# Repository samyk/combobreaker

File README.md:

# [C-C-C-C-Combo Breaker](http://samy.pl/combobreaker/)

**[Combo Breaker](http://samy.pl/combobreaker/)** is a motorized, battery powered, 3D printed, Arduino-based combination lock cracking device. It is portable, open source, 3D models provided, and exploits a new technique I've discovered for [cracking combination locks in 8 attempts or less](https://www.youtube.com/watch?v=09UgmwtL12c), but in an even more exciting, automated fashion.

By [@SamyKamkar](https://twitter.com/samykamkar)

#### Follow me on [Twitter](https://twitter.com/samykamkar) or [join my mailing list](http://samy.pl/list/) to hear about future projects and research.

**Live demonstration** and full details available in [the video](https://www.youtube.com/watch?v=YcpSvHpbHQ4):

-----

**Point of Contact:** [@SamyKamkar](https://twitter.com/samykamkar) // <http://samy.pl>

**Video demonstration / explanation:** [https://youtu.be/YcpSvHpbHQ4](https://youtu.be/YcpSvHpbHQ4)

**Released:** May 14, 2015

**Source code / 3D models:** [https://github.com/samyk/combobreaker](https://github.com/samyk/combobreaker)

**Unit Cost:** < $100

**Status:** Operational, open source, open hardware, declassified.

-----

# (U) Hardware

### [Arduino Nano](http://amzn.to/1QLlf23)
**$12**: A [5V Arduino Nano](http://amzn.to/1QLlf23) microcontroller is used as the brains of the project.

### [Allegro A3967 / EasyDriver Stepper Driver](http://amzn.to/1A1Ovxl)
**$20**: I originally used an A3967-based [EasyDriver](http://amzn.to/1A1Ovxl) which can drive a stepper motor up to 30V at 750mA. This is what precisely controls the dial.

### or [Allegro A4988](http://amzn.to/1L3q7fK)
**$7**: Instead of the EasyDriver, I upgraded to a smaller, yet more powerful stepper driver that can go up to 1 amp (1000mA).

### [Stepper Motor](http://amzn.to/1FfLUQG)
**$30**: You can use a normal stepper motor for the "simpler" version of the Combo Breaker build, however if you're working on creating the more advanced version, you'll need a double-shaft stepper motor like I liste below.

### or [Double Shaft Stepper Motor](http://www.phidgets.com/products.php?product_id=3320)
**$16**: This double shaft stepper motor allows you to build the more advanced Combo Breaker while employing an optical rotary encoder on the back to detect the position of the stepper when the dial stops turning (which is part of the exploit employed).

### [HKT22 Optical Rotary Encoder](http://www.phidgets.com/products.php?product_id=3531)
**$25**: For use **only** with the double shaft stepper motor, this optical rotary encoder lets us know what position the shaft of the stepper motor is at and allows us to employ an exploit on Master combination locks where the stepper will get locked into certain grooves within the internal combination disc of the lock.

### [Analog Feedback Servo](https://www.adafruit.com/products/1404)
**$15**: This servo not only provides the torque we need to lift the shackle (90.26 oz*in), but has an additional wire providing analog feedback that we use to detect the state of the shackle and whether it has opened or not.

### [L7805 Voltage Regulators](http://amzn.to/1A28XOt)
**$6**: If you're using the analog feedback servo, you'll want to use an external voltage regulator to provide enough juice to the servo. While the Arduino is 5V and can drive the servo normally, it won't be able to pump out enough current for the servo when it starts hitting the shackle and could damage your Arduino.

### [500mAh 3S Lipo Battery](http://amzn.to/1PkRVlz)
**$20**: This 500mAh 3S (3-cell, 11.1V) battery gives enough juice to the stepper motor to be very effective, and at 500mAh can last between 30-120minutes straight before having to be recharged.

### [Lipo Charger](http://amzn.to/1A1Q2n7)
**$50**: This lipo charger is overkill if only used for this project, but is a good one that I use at home for a wide range of batteries and cells. You don't need this one, but if you want to recharge the battery, you'll need a charger that supports 3-cell LiPos.

### [Arctic Alumina Thermal Adehsive](http://amzn.to/1PkTakG)
**$8**: Not required, but this is the thermal **adhesive** I use to **permanently** attach the heatsink to the stepper motor driver. Normal thermal paste has very little adhesion and kept falling off, so I switched from thermal paste to this thermal adhesive.

### [Digital Calipers](http://amzn.to/1K8juex)
**$16**: If you don't already have digital calipers for precise measurements to measure the lock, for example, these are inexpensive and accurate.

### [Breadboard and Wires](http://amzn.to/1FfMb6e)
**$6**: If you don't already have a breadboard and wires, they will kind of help.

-----

# (U) Software

### Combo Breaker
Combo Breaker's source code can be obtained in entirety from my github: <https://github.com/samyk/combobreaker>

-----

# (U) 3D Models

I've included the 3D models on my github: <https://github.com/samyk/combobreaker>

-----

# (U) Contact

**Point of Contact:** [@SamyKamkar](https://twitter.com/samykamkar)

You can see more of my projects at <http://samy.pl>.

#### Follow me on [Twitter](https://twitter.com/samykamkar) or [join my mailing list](http://samy.pl/list/) to hear about future projects and research.

Thanks!

------

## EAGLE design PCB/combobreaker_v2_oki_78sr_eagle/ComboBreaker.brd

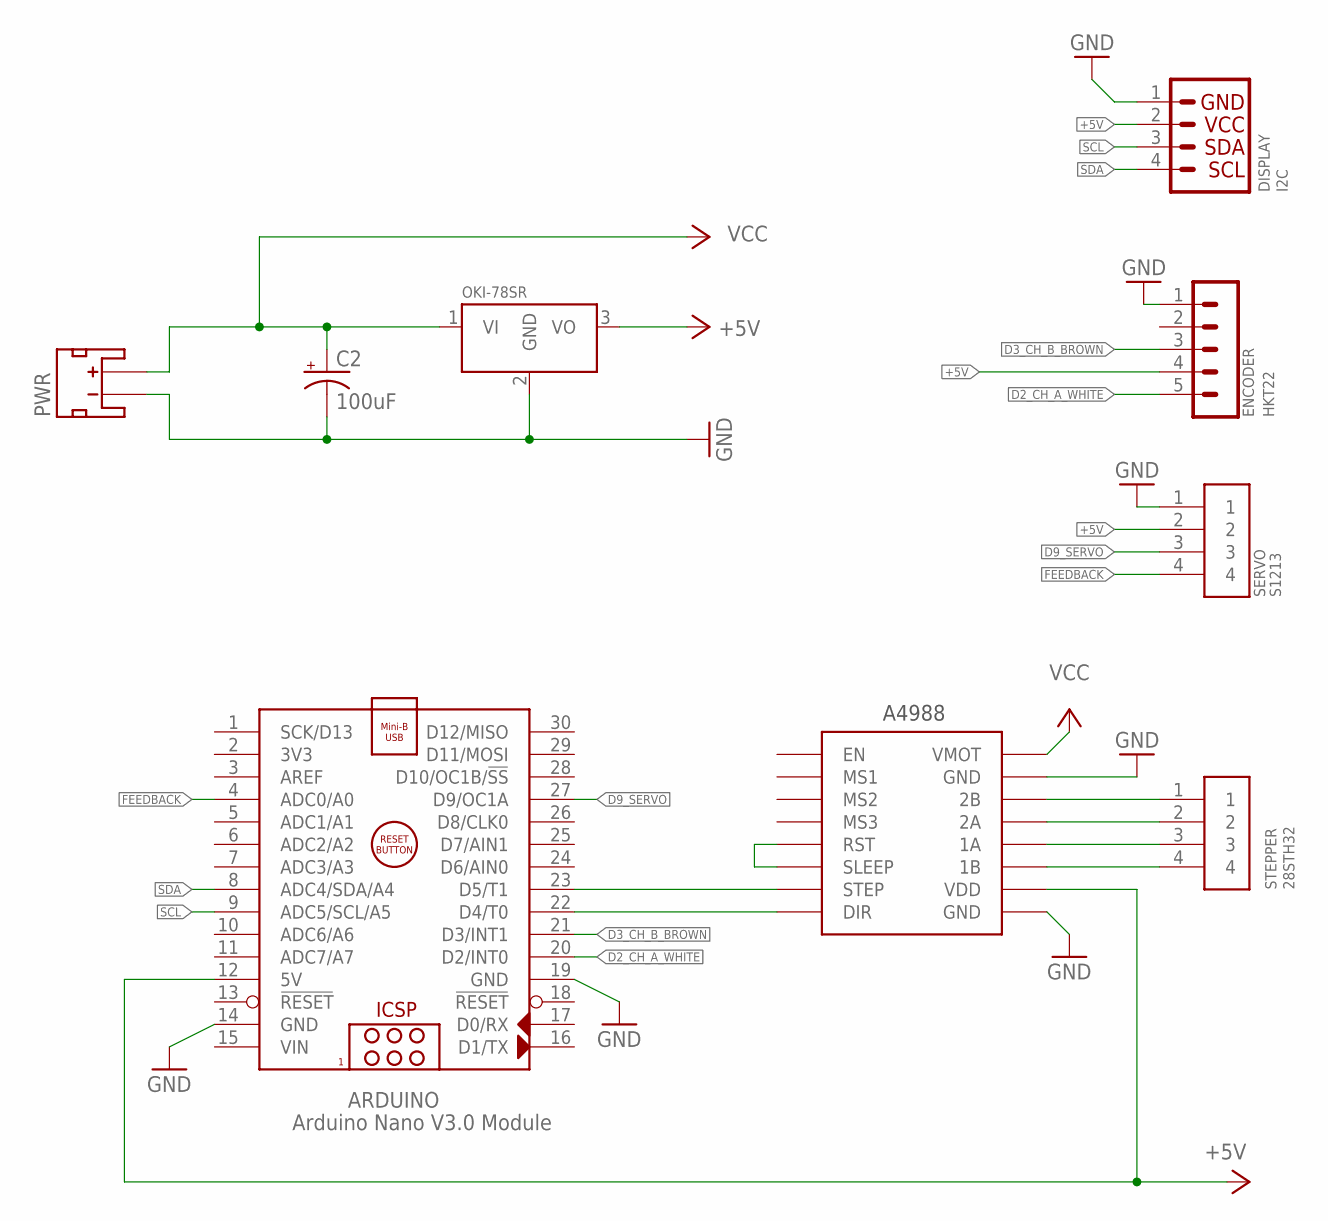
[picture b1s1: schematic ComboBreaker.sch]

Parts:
A4988: StepStick; A4988BREAKOUT
ARDUINO: Arduino Nano V3.0 Module; ARDUINO_NANO
C2: 100uF; E3,5-8
DISPLAY: I2C; 1X04
ENCODER: HKT22; CON-LSTB_MA05-1
OKI-78SR: 5/1.5-W36H-C; OKI-78SRH
PWR: 7-35v; JST-2-SMD
SERVO: S1213; ADAFRUIT_1X04-BIG
STEPPER: 28STH32; ADAFRUIT_1X04-BIG

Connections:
1A_GRN: A4988.1A, STEPPER.3
1B_BLK: A4988.1B, STEPPER.4
2A_RED: A4988.2A, STEPPER.2
2B_BLU: A4988.2B, STEPPER.1
+5V: A4988.VDD, ARDUINO.12 (5V), DISPLAY.2, ENCODER.4, OKI-78SR.3 (VO), SERVO.2
D2_CH_A_WHITE: ARDUINO.20 (D2/INT0), ENCODER.5
D3_CH_B_BROWN: ARDUINO.21 (D3/INT1), ENCODER.3
D9_SERVO: ARDUINO.27 (D9/OC1A), SERVO.3
FEEDBACK: ARDUINO.4 (ADC0/A0), SERVO.4
GND: A4988.GND, A4988.GND@0 (GND), ARDUINO.14 (GND), ARDUINO.19 (GND), C2.-, DISPLAY.1, ENCODER.1, OKI-78SR.2 (GND), PWR.GND (-), SERVO.1
unnamed: A4988.RST, A4988.SLP (SLEEP)
unnamed: A4988.DIR, ARDUINO.22 (D4/T0)
unnamed: A4988.STEP, ARDUINO.23 (D5/T1)
SCL: ARDUINO.9 (ADC5/SCL/A5), DISPLAY.3
SDA: ARDUINO.8 (ADC4/SDA/A4), DISPLAY.4
VCC: A4988.VMOT, C2.+, OKI-78SR.1 (VI), PWR.2 (+)
VIN: ARDUINO.15 (VIN)

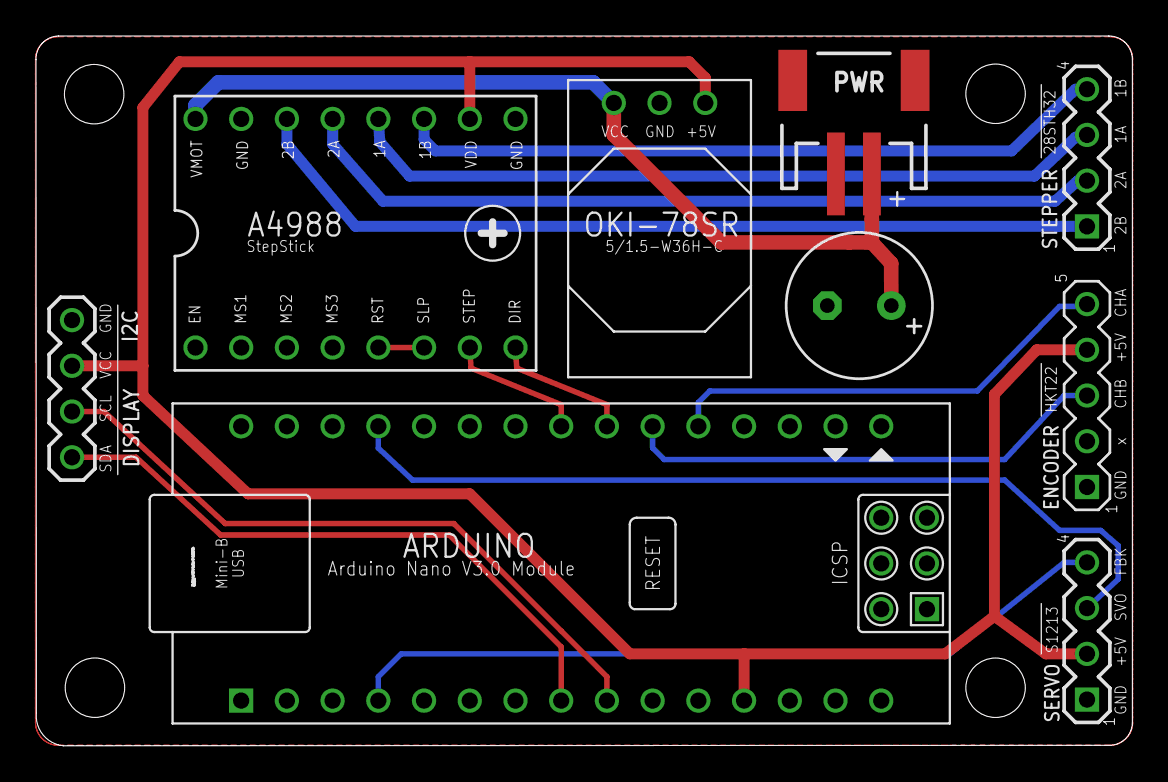
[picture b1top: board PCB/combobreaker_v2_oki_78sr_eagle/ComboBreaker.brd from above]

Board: 2 copper layers, 60.9 x 39.4 mm, 15 parts (1 on the bottom side), 16 nets.

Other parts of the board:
U$1, U$2, U$3, U$4: STAND-OFF
U$5: AM
U$6: MASTERLOCK2

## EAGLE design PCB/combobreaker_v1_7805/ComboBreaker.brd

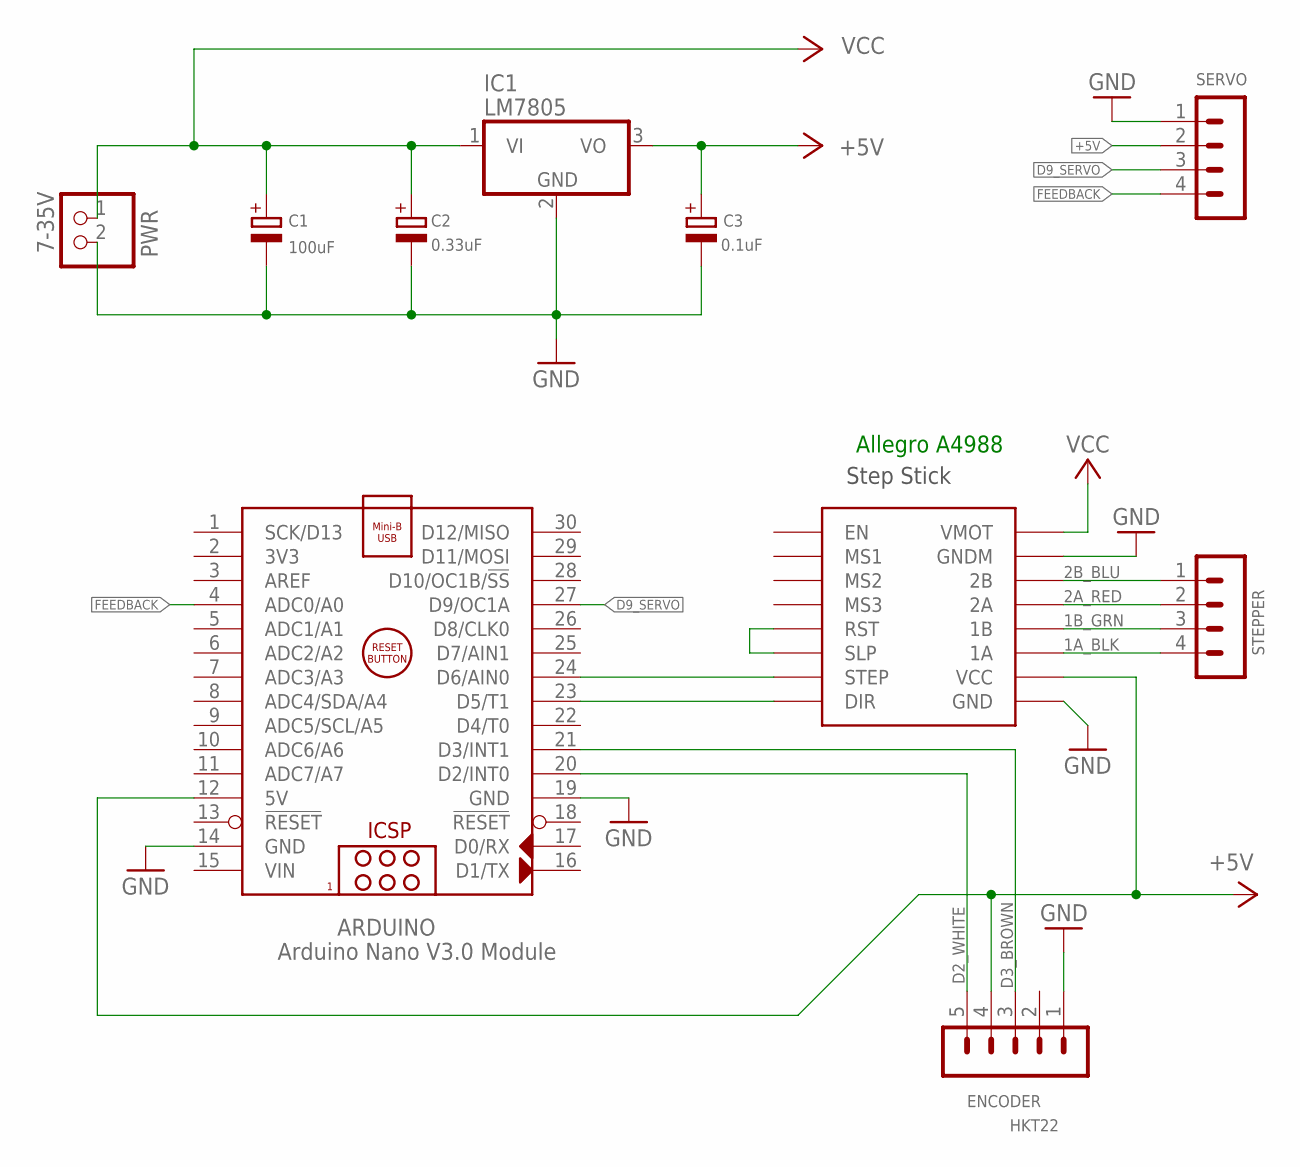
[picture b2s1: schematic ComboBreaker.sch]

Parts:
ARDUINO: Arduino Nano V3.0 Module; ARDUINO_NANO
C1: 100uF; E2-4
C2: 0.33uF; E2-4
C3: 0.1uF; E2-4
ENCODER: HKT22; MA05-1
IC1: LM7805; TO220V
PWR: 7-35V; JST-PH-2-SMT
SERVO: MA04-1
STEPPER: MA04-1
U$2: Allegro A4988; STEP-STICK

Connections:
1A_BLK: STEPPER.4, U$2.1A
1B_GRN: STEPPER.3, U$2.1B
2A_RED: STEPPER.2, U$2.2A
2B_BLU: STEPPER.1, U$2.2B
+5V: ARDUINO.12 (5V), C3.+, ENCODER.4, IC1.3 (VO), SERVO.2, U$2.VCC
D2_WHITE: ARDUINO.20 (D2/INT0), ENCODER.5
D3_BROWN: ARDUINO.21 (D3/INT1), ENCODER.3
D9_SERVO: ARDUINO.27 (D9/OC1A), SERVO.3
DIR: ARDUINO.23 (D5/T1), U$2.DIR
FEEDBACK: ARDUINO.4 (ADC0/A0), SERVO.4
GND: ARDUINO.14 (GND), ARDUINO.19 (GND), C1.-, C2.-, C3.-, ENCODER.1, IC1.2 (GND), PWR.2 (1), SERVO.1, U$2.GND, U$2.GNDM
RST_SLP: U$2.RST, U$2.SLP
STEP: ARDUINO.24 (D6/AIN0), U$2.SPT (STEP)
VCC: C1.+, C2.+, IC1.1 (VI), PWR.1 (2), U$2.VMOT
VIN: ARDUINO.15 (VIN)

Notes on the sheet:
Allegro A4988

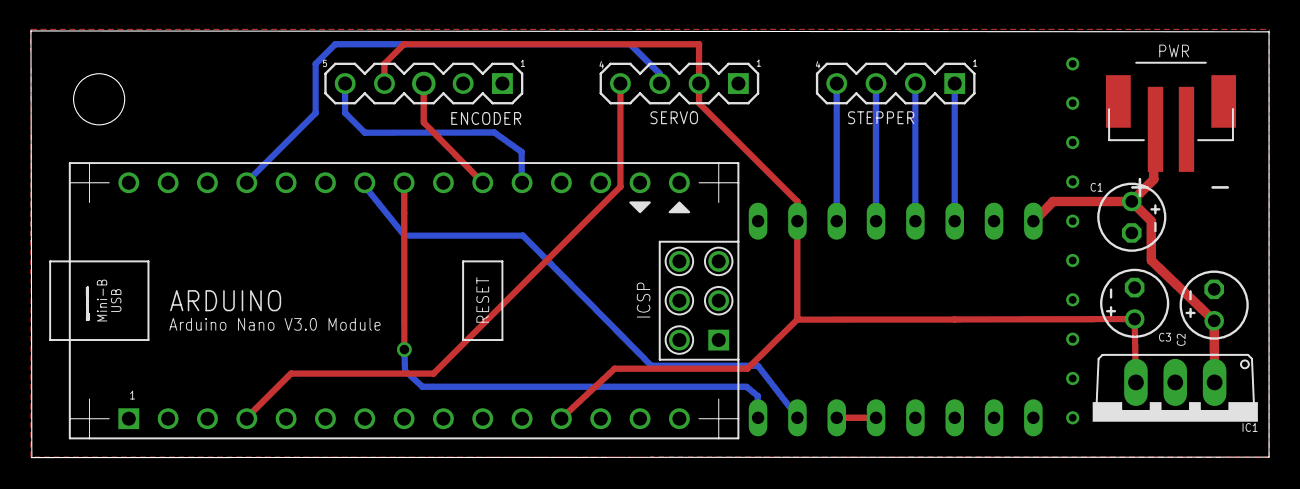
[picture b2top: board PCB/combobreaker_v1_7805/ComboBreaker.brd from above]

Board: 2 copper layers, 80.0 x 27.6 mm, 11 parts (0 on the bottom side), 14 nets.

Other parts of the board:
U$3: STAND-OFF

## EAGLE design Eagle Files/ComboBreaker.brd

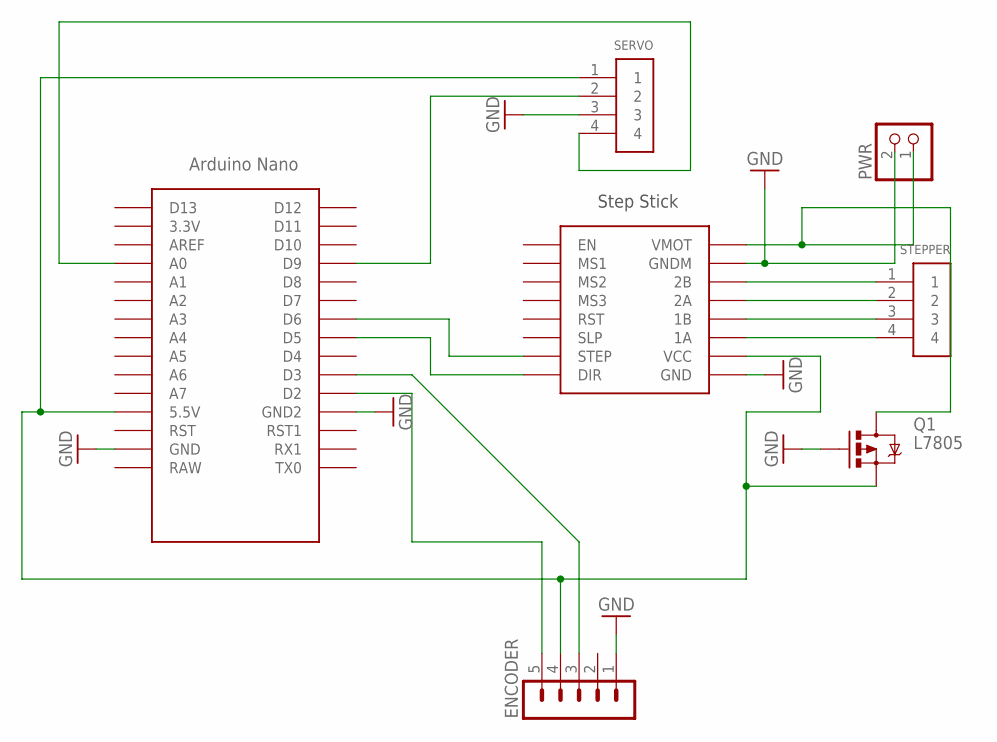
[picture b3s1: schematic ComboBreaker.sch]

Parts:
ENCODER: MA05-1
PWR: JST_2PIN-SMT; JST-PH-2-SMT
Q1: L7805; TO220V
SERVO: 1X4-BIG; 1X04-BIG
STEPPER: 1X4-BIG; 1X04-BIG
U$1: NANO
U$2: STEP-STICK

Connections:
GND: ENCODER.1, PWR.2 (1), Q1.1 (G), SERVO.3, U$1.GND, U$1.GND1 (GND2), U$2.GND, U$2.GNDM
unnamed: SERVO.2, U$1.D9
unnamed: U$1.D5, U$2.DIR
unnamed: U$1.D6, U$2.SPT (STEP)
unnamed: PWR.1 (2), Q1.2 (D), U$2.VMOT
unnamed: STEPPER.2, U$2.2A
unnamed: STEPPER.1, U$2.2B
unnamed: STEPPER.4, U$2.1A
unnamed: STEPPER.3, U$2.1B
unnamed: SERVO.4, U$1.A0
unnamed: ENCODER.5, U$1.D2
unnamed: ENCODER.4, Q1.3 (S), SERVO.1, U$1.5V (5.5V), U$2.VCC
unnamed: ENCODER.3, U$1.D3

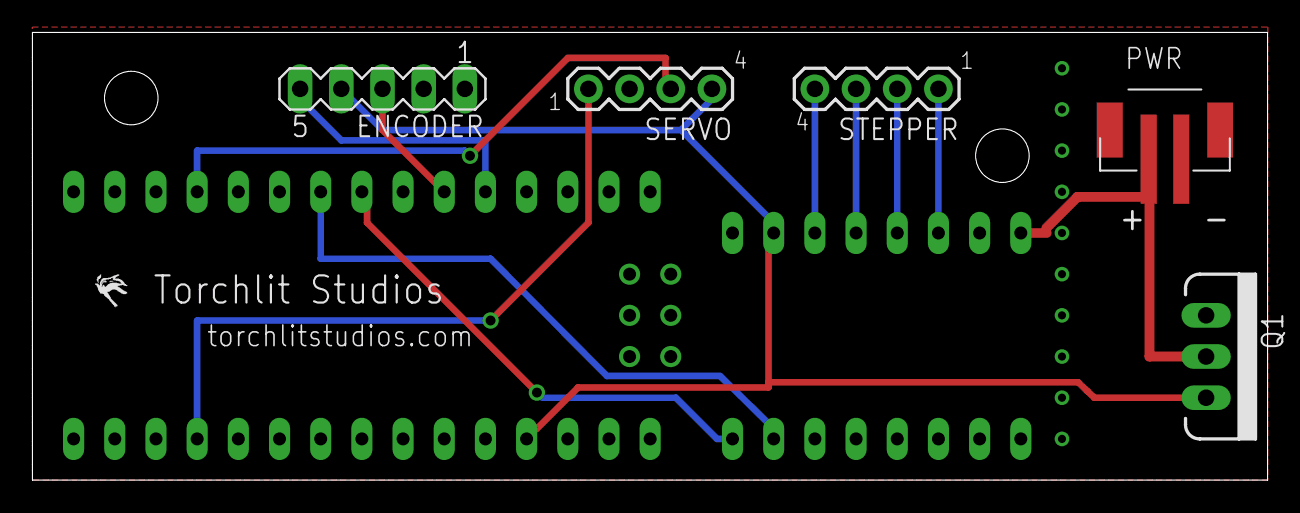
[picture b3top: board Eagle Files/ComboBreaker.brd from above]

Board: 2 copper layers, 76.2 x 27.6 mm, 9 parts (0 on the bottom side), 13 nets.

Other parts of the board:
U$3, U$4: STAND-OFF

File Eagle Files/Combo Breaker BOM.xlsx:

| JST-PH-2-SMT | https://www.sparkfun.com/products/8612?gclid=CjwKEAjwovytBRC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
 | L7805CV | http://www.mouser.com/ProductDetail/STMicroelectronics/L7805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
 | STEP-STICK | http://www.ebay.com/itm/like/281574528914?lpid=82&chn=ps
 | Arduino Nano | http://www.newegg.com/Product/Product.aspx?Item=9SIA7BF2K191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
 | Pin Headers | https://www.sparkfun.com/products/116

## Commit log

2015-05-14 Added code + 3d models
2015-05-14 finishing up rest
2015-05-14 new pretty pictures
2015-05-14 fixed date
2015-05-14 mo money mo gitcommits
2015-05-17 added f3d (fusion 360 archive file) for the chassis
2015-05-17 added f3d (fusion 360 archive file) for pancake stepper gripper
2015-08-03 Initial Commit
    Still requires verification and testing. Do not build until tested!
2015-08-03 added picture
2015-08-03 Finished Design
    Added Encoder header and verified design against documentation.
    releasing for first piece prototype. please report any errors.
2015-08-04 prettied up
    prettied things up and added some pictures and BOM
2015-08-04 Added Standoff Holes
    #4 Philips standoff holes added to board
2015-08-04 added stl files
    stl files added for 3d printing
2016-11-13 Update prices
2017-03-15 PCB with OKI-78SR
    * Corrected pinouts for LM7805
    * Replaced LM7805 with OKI-78SR switching regulator. This is a “No heat
    sink” direct replacement for 3-terminal 78xx-series linear regulators.
    * Added 100uf decoupling capacitor
    * Updated Arduino Nano device/footprint
    * Updated A4988 StepStep device/footprint
2017-03-15 PCB with LM7805
    * Added decoupling capacitor
    * Updated Arduino Nano device/footprint
    * Updated A4988 StepStep device/footprint
    * Added trace between RST and SLP on A4988
    * Corrected pinouts for LM7805
2017-03-15 PCB with OKI-78SR
    *** Converted EAGLE files to kicad ***
    * Replaced LM7805 with OKI-78SR switching regulator. This is a “No heat
    sink” direct replacement for 3-terminal 78xx-series linear regulators.
    * Added 100uf decoupling capacitor
    * Updated Arduino Nano device/footprint
    * Updated A4988 StepStep device/footprint
2017-03-16 Added I2C OLED Display
    * Added I2C header pins for OLED display
    * Reoriented JST power connector
    * Rerouted VCC
2017-03-19 Updated v2 Eagle PCB layout
    * Added standoff holes
    * Added descriptions
    * Added mitre to board corners
2017-03-19 Updated PCB
    * Moved silkscreen text to tPlace layer
    * Moved holes in Arduino Nano module to Reference layer
2017-03-20 Updated v2 Eagle PCB
    * Added more silkscreen details
    * Minor adjustments to footprints
    TO-DO:
    * Confirm pinout wire colors
2017-03-20 Updated v2 Eagle PCB (Prototype Ordered!)
    This is final prototype design sent to printers!
    * Added Master Lock logo
    * Added pinout wire colors to bottom silkscreen
    * Added pin identifiers to servo/stepper/encoder pins on top silkscreen
    * Redraw ground pour polygons
2017-03-23 Set theme jekyll-theme-minimal
2017-03-31 Update v2 Eagle PCB
    * Fix drill hole size on header pin package
2017-04-05 Updated v2 Eagle PCB
    * Renamed Stepper pinout labels
    * Added ground connections
    * Manually set MIN_DELAY
2017-05-08 Updated ComboBreaker.ino code
    * Corrected DIR and STEP pins
    * Added delayMicroseconds(MIN_DELAY); to line 362 which resolved the
    issue with the stepper motor not stepping correctly
2017-09-06 Replace mod() with % operator
2017-09-25 Added GND pour to TOP layer
    *** Added GND pour to TOP layer to resolve issues with SMD JST connector etc.
    *** Adjusted JST connector pin name to GND.
2017-09-25 Minor changes to schematic
2017-09-28 Updated header pins to circles from ovals
2017-10-05 Updated drill size to .35
    * Updated drill sizes on most holes to .35
    * Adjusted Mini-B USB connector outline on Arduino Nano silkscreen
2017-10-06 v3 PCB
    Minor changes
    V3 send to fabrication
2018-12-22 VSCode
2018-12-22 Adding .DS_Store to ignore list
2019-04-08 Adding .DS_Store

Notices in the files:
parts and their libraries:
User-Submitted: Licensing: Creative Commons ShareAlike 4.0 International - https://creativecommons.org/licenses/by-sa/4.0
